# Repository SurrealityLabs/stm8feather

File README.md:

# stm8feather
A Feather board for STM8 microcontrollers

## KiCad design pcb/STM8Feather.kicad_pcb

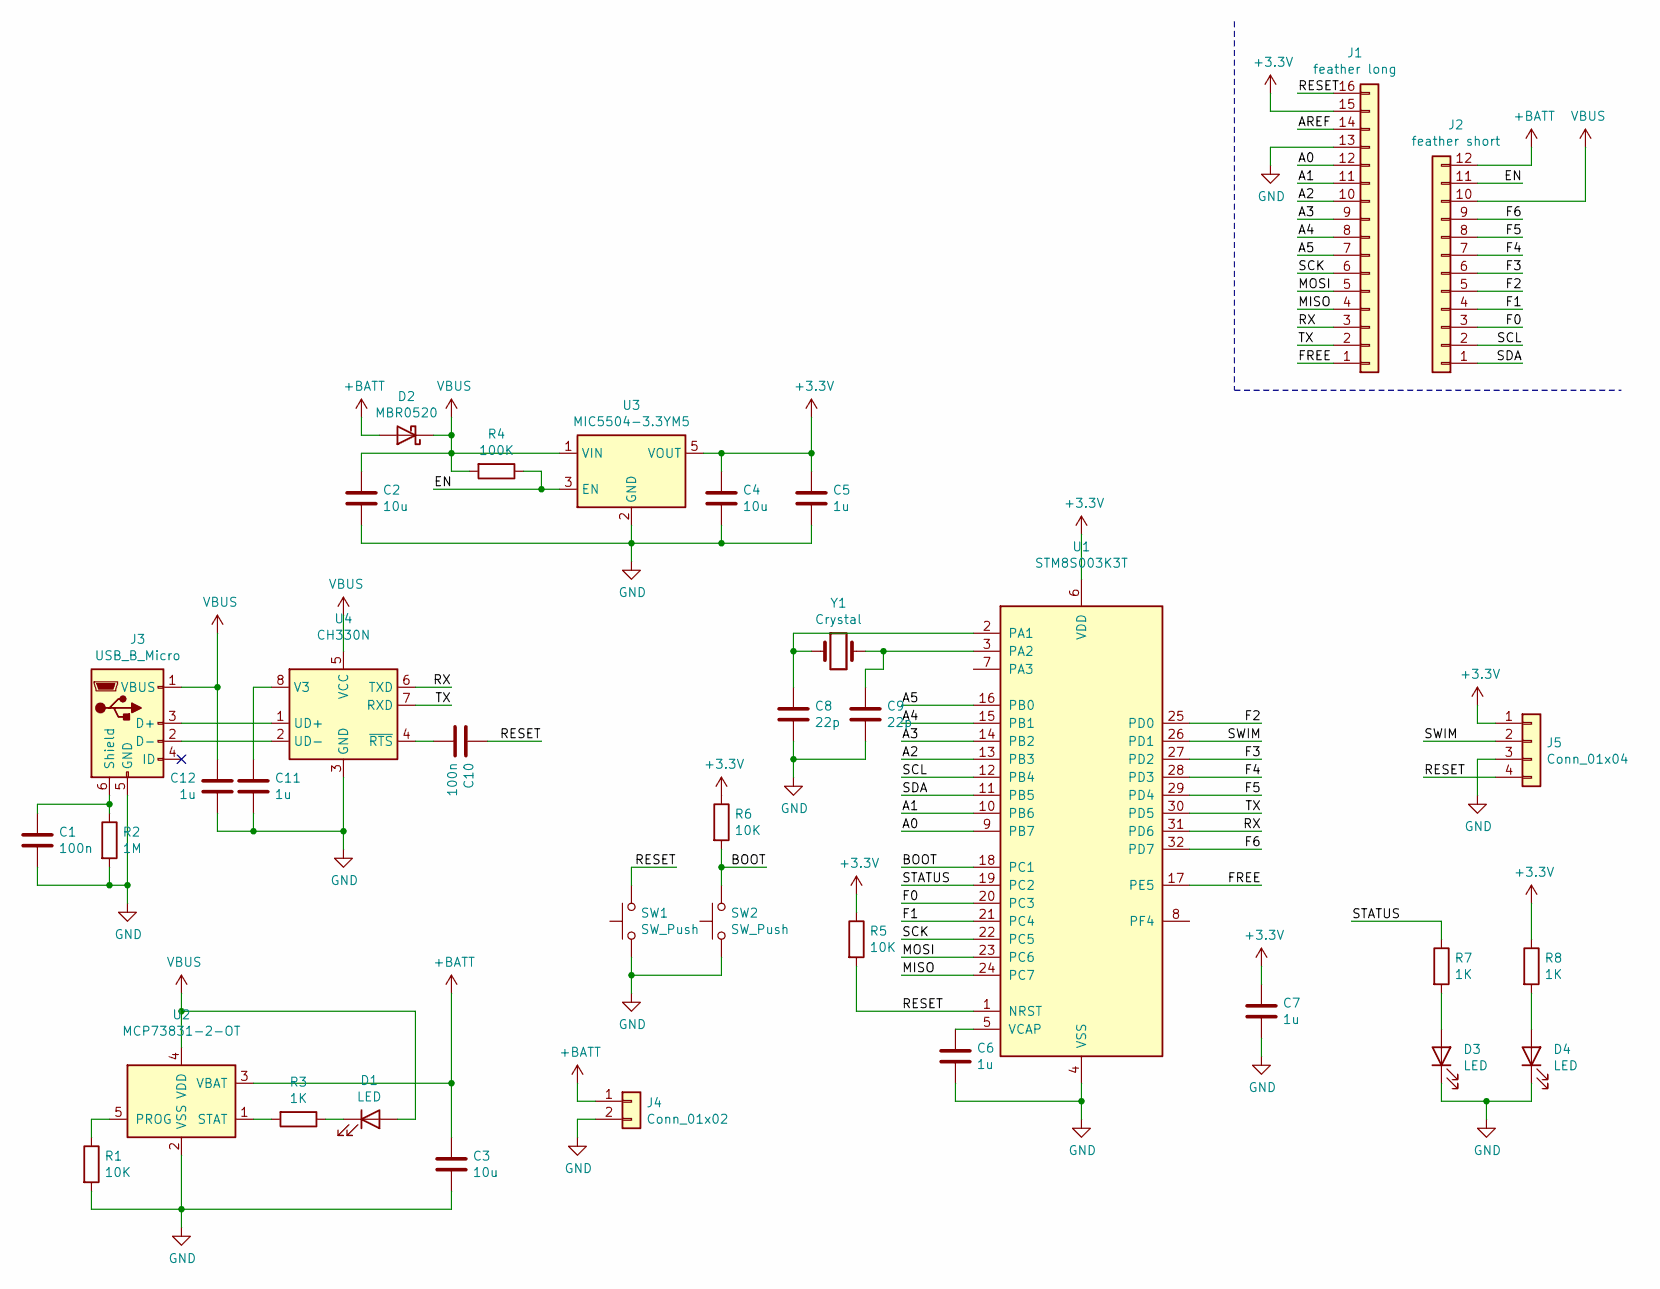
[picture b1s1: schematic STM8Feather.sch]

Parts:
C1, C10: 100n; C_0603_1608Metric
C2, C3, C4: 10u; C_0805_2012Metric
C5, C6, C7, C11, C12: 1u; C_0603_1608Metric
C8, C9: 22p; C_0603_1608Metric
D1, D3, D4: LED; LED_0603_1608Metric
D2: MBR0520; D_SOD-123
J1: feather long; PinHeader_1x16_P2.54mm_Vertical
J2: feather short; PinHeader_1x12_P2.54mm_Vertical
J3: USB_B_Micro; USB_Micro-B_Molex_47346-0001
J4: Conn_01x02; JST_PH_S2B-PH-SM4-TB_1x02-1MP_P2.00mm_Horizontal
J5: Conn_01x04; PinHeader_1x04_P2.54mm_Vertical
R1, R5, R6: 10K; R_0603_1608Metric
R2: 1M; R_0603_1608Metric
R3, R7, R8: 1K; R_0603_1608Metric
R4: 100K; R_0603_1608Metric
SW1, SW2: SW_Push; SW_Push_SPST_NO_Alps_SKRK
U1: STM8S003K3T; LQFP-32_7x7mm_P0.8mm
U2: MCP73831-2-OT; SOT-23-5
U3: MIC5504-3.3YM5; SOT-23-5
U4: CH330N; SOIC-8_3.9x4.9mm_P1.27mm
Y1: Crystal; Crystal_SMD_HC49-SD

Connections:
+3V3: C4.1, C5.1, C7.1, J1.15, J5.1, R5.1, R6.1, R8.1, U1.6 (VDD), U3.5 (VOUT)
+BATT: C3.1, D2.2 (A), J2.12, J4.1, U2.3 (VBAT)
/A0: J1.12, U1.9 (PB7)
/A1: J1.11, U1.10 (PB6)
/A2: J1.10, U1.13 (PB3)
/A3: J1.9, U1.14 (PB2)
/A4: J1.8, U1.15 (PB1)
/A5: J1.7, U1.16 (PB0)
/BOOT: R6.2, SW2.2, U1.18 (PC1)
/EN: J2.11, R4.1, U3.3 (EN)
/F0: J2.3, U1.20 (PC3)
/F1: J2.4, U1.21 (PC4)
/F2: J2.5, U1.25 (PD0)
/F3: J2.6, U1.27 (PD2)
/F4: J2.7, U1.28 (PD3)
/F5: J2.8, U1.29 (PD4)
/F6: J2.9, U1.32 (PD7)
/FREE: J1.1, U1.17 (PE5)
/MISO: J1.4, U1.24 (PC7)
/MOSI: J1.5, U1.23 (PC6)
/RESET: C10.1, J1.16, J5.4, R5.2, SW1.2, U1.1 (NRST)
/RX: J1.3, U1.31 (PD6), U4.6 (TXD)
/SCK: J1.6, U1.22 (PC5)
/SCL: J2.2, U1.12 (PB4)
/SDA: J2.1, U1.11 (PB5)
/STATUS: R7.1, U1.19 (PC2)
/SWIM: J5.2, U1.26 (PD1)
/TX: J1.2, U1.30 (PD5), U4.7 (RXD)
GND: C1.2, C2.2, C3.2, C4.2, C5.2, C6.2, C7.2, C8.2, C9.2, C11.2, C12.2, D3.1 (K), D4.1 (K), J1.13, J3.5 (GND), J4.2, J5.3, R1.2, R2.2, SW1.1, SW2.1, U1.4 (VSS), U2.2 (VSS), U3.2 (GND), U4.3 (GND)
unnamed: C1.1, J3.6 (Shield), R2.1
unnamed: C6.1, U1.5 (VCAP)
unnamed: C8.1, U1.2 (PA1), Y1.1
unnamed: C9.1, U1.3 (PA2), Y1.2
unnamed: C10.2, U4.4 (~RTS)
unnamed: C11.1, U4.8 (V3)
unnamed: D1.1 (K), R3.1
unnamed: D3.2 (A), R7.2
unnamed: D4.2 (A), R8.2
unnamed: J3.2 (D-), U4.2 (UD-)
unnamed: J3.3 (D+), U4.1 (UD+)
unnamed: R1.1, U2.5 (PROG)
unnamed: R3.2, U2.1 (STAT)
VBUS: C2.1, C12.1, D1.2 (A), D2.1 (K), J2.10, J3.1 (VBUS), R4.2, U2.4 (VDD), U3.1 (VIN), U4.5 (VCC)

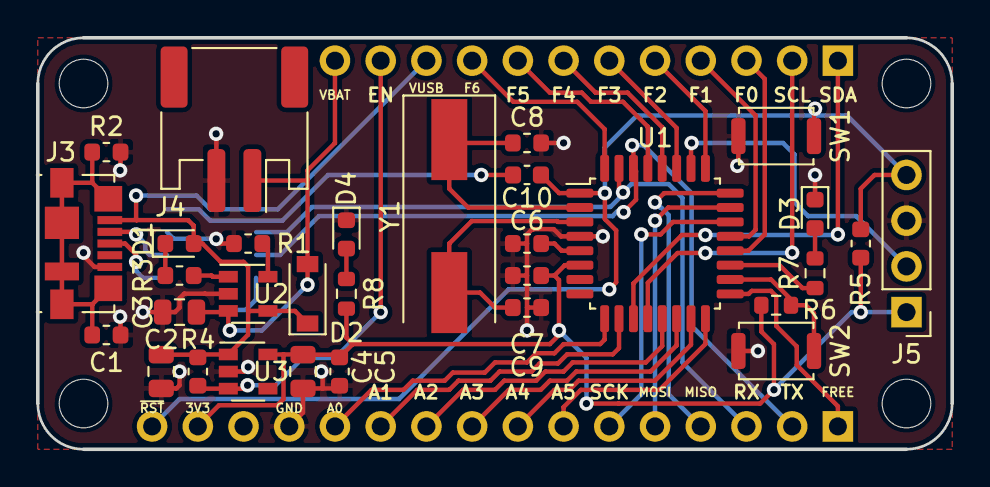
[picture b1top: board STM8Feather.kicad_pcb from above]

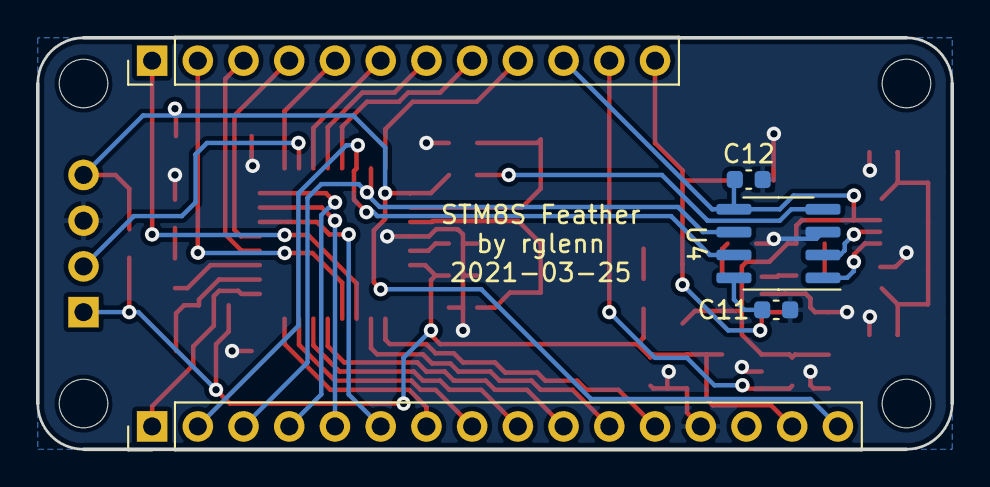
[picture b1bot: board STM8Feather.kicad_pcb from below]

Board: 2 copper layers, 50.8 x 22.9 mm, 36 parts (5 on the bottom side), 43 nets.

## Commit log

2021-03-21 Adding existing PCB work
2021-03-26 Adding status LED, reset button, boot button, and power LED
2021-03-28 Updating manufacturing data
